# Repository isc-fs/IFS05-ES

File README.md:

# IFS05 - ELECTRONIC SUBSYSTEMS

Repositorio para el departamento de Electronic Subsystems del IFS05 de la temporada 2022/2023.

## Primeros pasos:
1. Crea una cuenta en GitHub si aún no tienes una.
2. Descarga e instala [GitHub Desktop](https://desktop.github.com/) (básico) o [Git CLI](https://git-scm.com/book/en/v2/Getting-Started-Installing-Git) (avanzado).

    * Si es la primera vez que utilizas GitHub Desktop, asegúrate de leer el [Manual del usuario](https://help.github.com/desktop/guides/).
    * Si estás usando Git por primera vez, deberías empezar leyendo un tutorial. Hay muchos disponibles en línea:
        * [Tutorial de Git](https://git-scm.com/docs/gittutorial)
        * [Atlassian Git Tutorial](https://www.atlassian.com/git/tutorials/)
    * Puede que quieras guardar una copia de [GitHub's Git Cheat Sheet](https://services.github.com/kit/downloads/github-git-cheat-sheet.pdf) como referencia.

3. Habla con tu jefe de departamento para que te añada al equipo dentro de la organización de GitHub.
4. Clona este repositorio en tu ordenador utilizando las URLs:
    * SSH: `git@github.com:isc-fs/IFS05-ES.git`
    * HTTPS: `https://github.com/isc-fs/IFS05-ES.git`

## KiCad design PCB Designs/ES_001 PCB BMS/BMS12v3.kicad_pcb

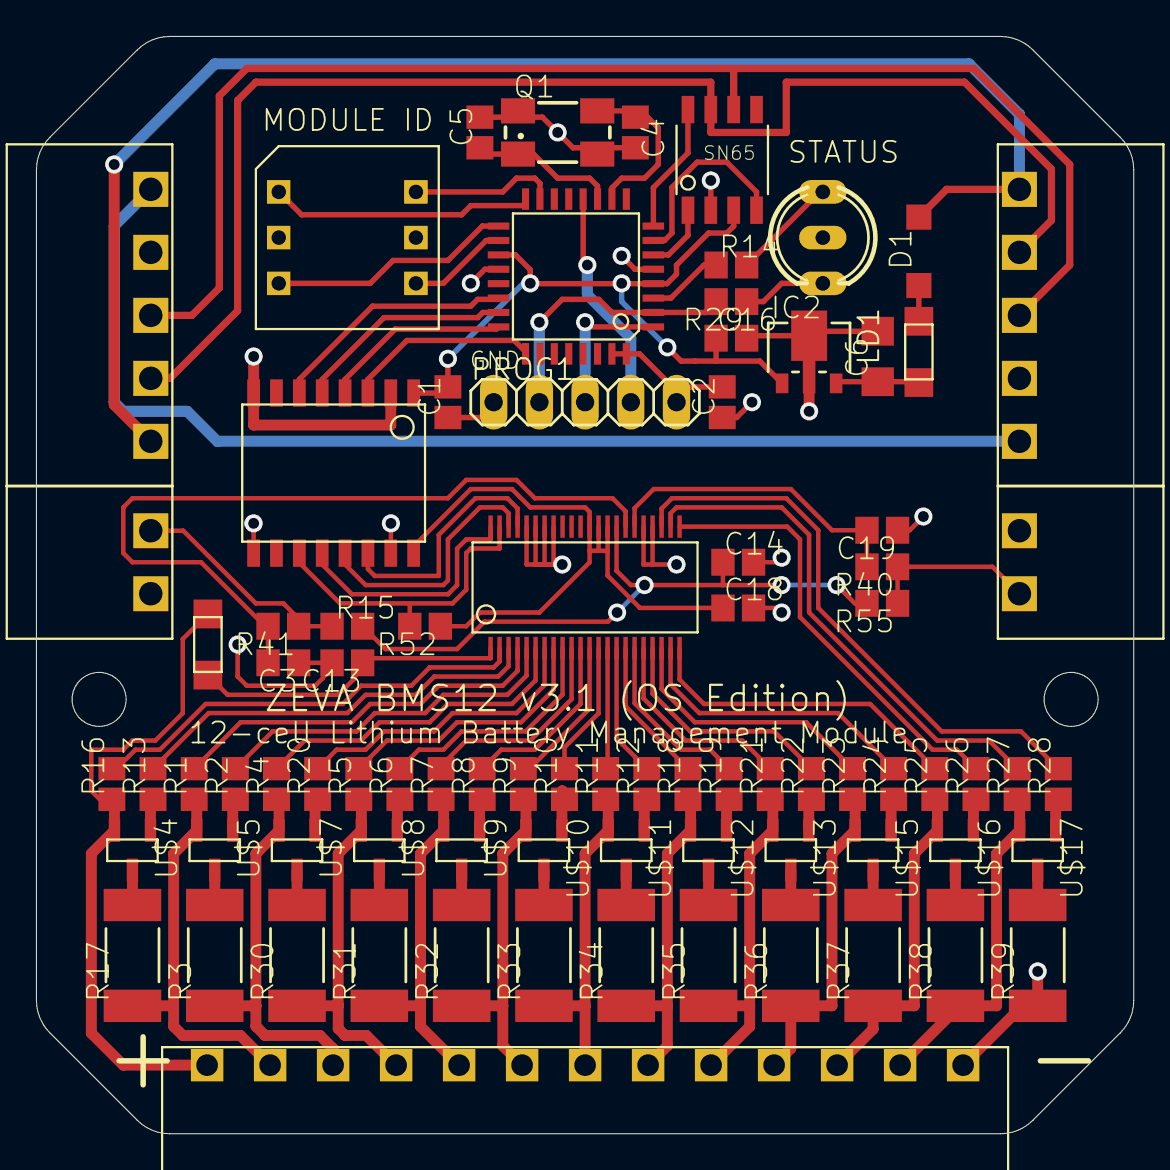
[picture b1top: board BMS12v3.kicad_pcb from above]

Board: 2 copper layers, 61.0 x 61.0 mm, 85 parts (0 on the bottom side), 100 nets.

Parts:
@HOLE0, @HOLE1: (no value)
C1, C2, C3, C13, C14, C18, C19: 0.1uF; C0805
C4, C5: 10pF; C0805
C6: 47uF; C1206
C16: 1uF; C0805
D1: DIODE-SOD123; SOD123
IC2: 78LXXSOT89; SOT89R
LD1: DUOLED-RG-C; DUOLED-C-5MM
PROG1: PINHD-1X5; 1X05
Q1: CRYSTALCTS406; CTS406
R1, R2, R4, R5, R6, R7, R8, R9, R10, R11, R12, R13, R14, R16, R18, R19, R20, R21, R22, R23, R24, R25, R26, R27, R28, R29: 3.3K; R0805
R3, R17, R30, R31, R32, R33, R34, R35, R36, R37, R38, R39: 50R; R2512
R15, R40, R41, R52, R55: 100K; R0805
SN65: L9616; SOIC8
U$1: LTC6802-2; SSOP-44
U$2, U$19: MOLEX-39502-1005
U$3: ATMEGA16M1; TQFP32
U$4, U$5, U$7, U$8, U$9, U$10, U$11, U$12, U$13, U$15, U$16, U$17: SI2351DS; SOT23
U$6, U$28: 50mA PTC; 1206
U$14: ADUM1411; SOIC16W
U$18: MOLEX_TERM_BLOCK_13
U$20, U$21: MOLEX-39502-1002
U$31: SH-7000WURTH; WS-ROTV

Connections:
+5V: C1.2, C16.1, IC2.2 (OUT), SN65.P$3 (VS), U$3.4 (VCC), U$3.19 (AVCC), U$14.1 (VDD1)
+12V: D1.A, U$2.1, U$19.1
/VIA: U$3.25 (PC7(D2A/AMP2+)), U$14.3 (VIA)
/VIB: U$3.24 (PB4(AMP0+)), U$14.4 (VIB)
/VIC: U$3.23 (PB3(AMP0-)), U$14.5 (VIC)
/VOD: U$3.22 (PC6(ADC10/ACMP1)), U$14.6 (VOD)
AGND: C3.1, C13.2, C14.2, C18.2, C19.1, R39.1, U$1.26 (V-), U$1.27 (NC), U$1.37 (A0), U$1.38 (A1), U$1.39 (A2), U$1.40 (A3), U$14.9 (GND2B), U$14.15 (GND2), U$18.13, U$20.1, U$21.1
GND: C1.1, C2.1, C4.2, C5.2, C6.2, C16.2, IC2.4 (GND), LD1.C, PROG1.1, SN65.P$2 (GND), U$2.4, U$3.5 (GND), U$3.20 (AGND), U$14.2 (GND1), U$14.8 (GND1B), U$19.4, U$31.C, U$31.C2 (C_)
unnamed: C2.2, PROG1.5, U$3.31 (PE0(/RESET)), U$3.32 (PD1(PSCIN0/CLK0))
unnamed: C3.2, R41.2, U$1.29 (VTEMP2)
unnamed: C4.1, Q1.3 (2), U$3.10 (PE1(XTAL1/OC0B))
unnamed: C5.1, Q1.1, U$3.11 (PE2(XTAL2/ADC0))
unnamed: C6.1, IC2.1 (IN), U$28.P$2
unnamed: C13.1, U$1.1 (V+), U$6.P$2
unnamed: C14.1, R15.2, R55.2, U$1.30 (VREF)
unnamed: C18.1, R52.1, U$1.31 (VREG), U$1.32 (TOS), U$1.33 (MMB), U$14.16 (VDD2)
unnamed: C19.2, R40.2, U$1.28 (VTEMP1)
unnamed: D1.C, U$28.P$1
unnamed: LD1.AR, R29.1
unnamed: LD1.AX (AG), R14.2
unnamed: PROG1.2, R29.2, U$3.2 (PD3(TXLIN/OC0A/SS/MOSI_A))
unnamed: PROG1.3, U$3.1 (PD2(PSCIN2/OC1A/MISO_A))
unnamed: PROG1.4, U$3.12 (PD4(ADC1/RXD/RXLIN/ICP1A/SCK_A))
unnamed: R1.1, R17.1, U$5.P$2 (S), U$18.2
unnamed: R1.2, U$1.4 (C11)
unnamed: R2.1, U$5.P$1 (G)
unnamed: R2.2, U$1.5 (S11)
unnamed: R3.1, R4.1, U$7.P$2 (S), U$18.3
unnamed: R3.2, U$5.P$3 (D)
unnamed: R4.2, U$1.6 (C10)
unnamed: R5.2, U$1.8 (C9)
unnamed: R6.1, U$8.P$1 (G)
unnamed: R6.2, U$1.9 (S9)
unnamed: R7.2, U$1.10 (C8)
unnamed: R8.1, U$9.P$1 (G)
unnamed: R8.2, U$1.11 (S8)
unnamed: R9.2, U$1.12 (C7)
unnamed: R10.1, U$10.P$1 (G)
unnamed: R10.2, U$1.13 (S7)
unnamed: R11.1, R33.1, U$11.P$2 (S), U$18.7
unnamed: R11.2, U$1.14 (C6)
unnamed: R12.1, U$11.P$1 (G)
unnamed: R12.2, U$1.15 (S6)
unnamed: R13.1, U$4.P$1 (G)
unnamed: R13.2, U$1.3 (S12)
unnamed: R14.1, U$3.3 (PC1(PSCIN1/OC1B/SS_A))
unnamed: R15.1, R41.1, U$21.2
unnamed: R16.1, U$4.P$2 (S), U$6.P$1, U$18.1
unnamed: R16.2, U$1.2 (C12)
unnamed: R17.2, U$4.P$3 (D)
unnamed: R18.1, R34.1, U$12.P$2 (S), U$18.8
unnamed: R18.2, U$1.16 (C5)
unnamed: R19.1, U$12.P$1 (G)
unnamed: R19.2, U$1.17 (S5)
unnamed: R20.1, U$7.P$1 (G)
unnamed: R20.2, U$1.7 (S10)
unnamed: R21.1, R35.1, U$13.P$2 (S), U$18.9
unnamed: R21.2, U$1.18 (C4)
unnamed: R22.1, U$13.P$1 (G)
unnamed: R22.2, U$1.19 (S4)
unnamed: R23.1, R36.1, U$15.P$2 (S), U$18.10
unnamed: R23.2, U$1.20 (C3)
unnamed: R24.1, U$15.P$1 (G)
unnamed: R24.2, U$1.21 (S3)
unnamed: R25.1, R37.1, U$16.P$2 (S), U$18.11
unnamed: R25.2, U$1.22 (C2)
unnamed: R26.1, U$16.P$1 (G)
unnamed: R26.2, U$1.23 (S2)
unnamed: R27.1, R38.1, U$17.P$2 (S), U$18.12
unnamed: R27.2, U$1.24 (C1)
unnamed: R28.1, U$17.P$1 (G)
unnamed: R28.2, U$1.25 (S1)
unnamed: R5.1, R30.1, U$8.P$2 (S), U$18.4
unnamed: R30.2, U$7.P$3 (D)
unnamed: R7.1, R31.1, U$9.P$2 (S), U$18.5
unnamed: R31.2, U$8.P$3 (D)
unnamed: R9.1, R32.1, U$10.P$2 (S), U$18.6
unnamed: R32.2, U$9.P$3 (D)
unnamed: R33.2, U$10.P$3 (D)
unnamed: R34.2, U$11.P$3 (D)
unnamed: R35.2, U$12.P$3 (D)
unnamed: R36.2, U$13.P$3 (D)
unnamed: R37.2, U$15.P$3 (D)
unnamed: R38.2, U$16.P$3 (D)
unnamed: R39.2, U$17.P$3 (D)
unnamed: R40.1, R55.1, U$20.2
unnamed: R52.2, U$1.43 (SDO), U$14.11 (VID)
unnamed: SN65.P$1 (TX0), U$3.6 (PC2(T0/TXCAN))
unnamed: SN65.P$4 (RX0), U$3.7 (PC3(T1/RXCAN/ICP1B))
unnamed: SN65.P$6 (C_L), U$2.3, U$19.3
unnamed: SN65.P$7 (C_H), U$2.2, U$19.2
unnamed: SN65.P$8 (ASC), U$3.8 (PB0(MISO/PSCOUT2A))
unnamed: U$1.41 (SCKI), U$14.14 (VOA)
unnamed: U$1.42 (SDI), U$14.13 (VOB)
unnamed: U$1.44 (CSBI), U$14.12 (VOC)
unnamed: U$3.15 (PD7(ACMP0)), U$31.8
unnamed: U$3.16 (PB2(ADC5/INT1/ACMPN0)), U$31.1
unnamed: U$3.17 (PC4(ADC8/ACMPN3/AMP1-)), U$31.4
unnamed: U$3.18 (PC5(ADC9/ACMP3/AMP1+)), U$31.2
unnamed: U$2.5, U$19.5

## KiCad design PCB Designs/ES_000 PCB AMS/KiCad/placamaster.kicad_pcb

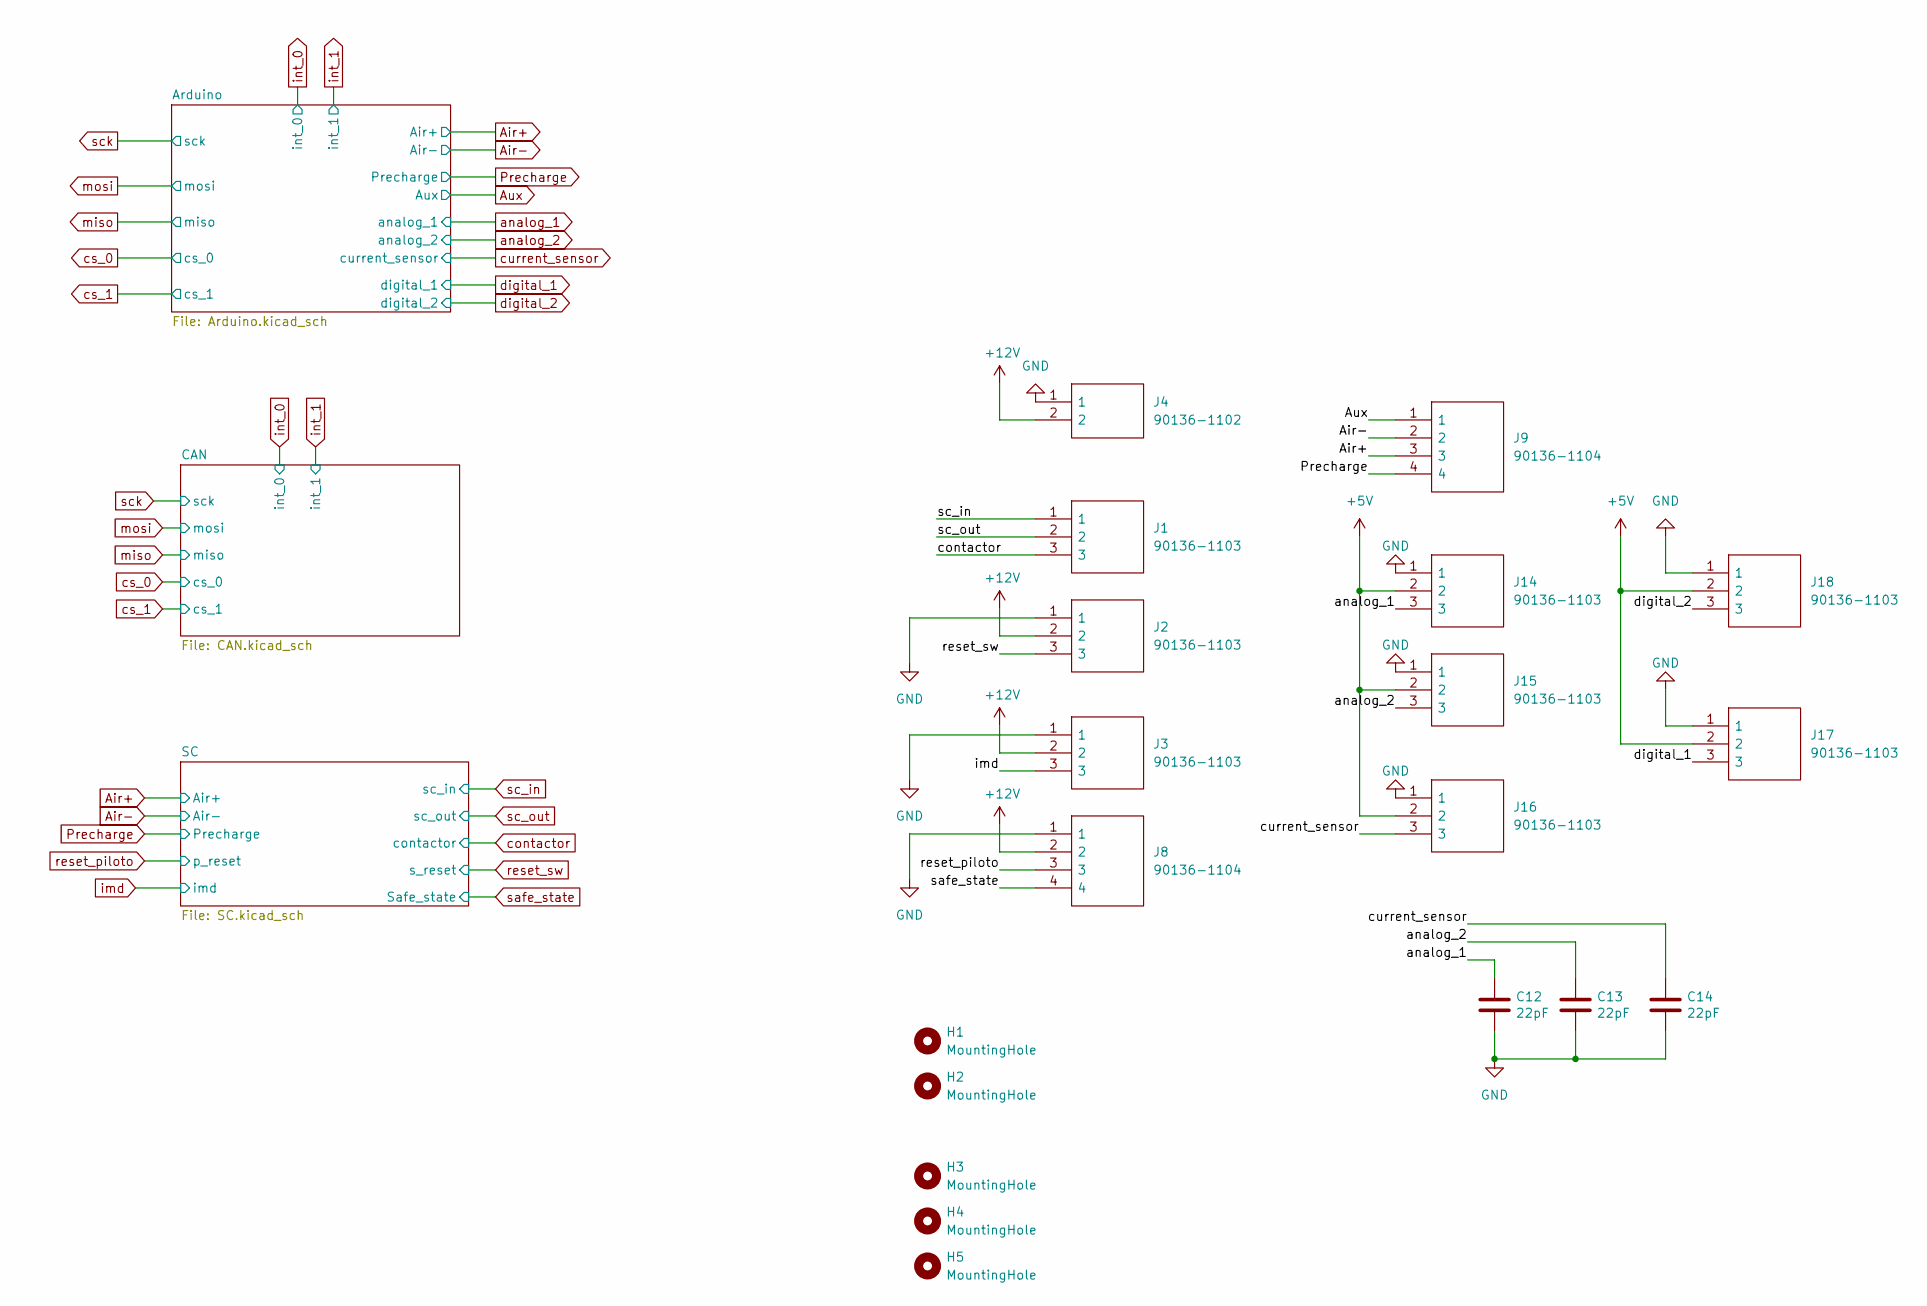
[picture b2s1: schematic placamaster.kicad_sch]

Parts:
C12, C13, C14: 22pF; C_0805_2012Metric_Pad1.18x1.45mm_HandSolder
H1, H2, H3, H4, H5: MountingHole
J1, J2, J3, J14, J15, J16, J17, J18: 90136-1103; SHDR3W65P0X254_1X3_1097X721X1110P; Mouser Part Number 538-90136-1103
J4: 90136-1102; SHDR2W65P0X254_1X2_843X721X1110P; Mouser Part Number 538-90136-1102
J8, J9: 90136-1104; SHDR4W65P0X254_1X4_1351X721X1110P; Mouser Part Number 538-90136-1104

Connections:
+5V: J14.2, J15.2, J16.2, J17.2, J18.2; also elsewhere on the board
+12V: J2.2, J3.2, J4.2, J8.2; also elsewhere on the board
Air+: J9.3; also elsewhere on the board
Air-: J9.2; also elsewhere on the board
Aux: J9.1; also elsewhere on the board
GND: C12.2, C13.2, C14.2, J2.1, J3.1, J4.1, J8.1, J14.1, J15.1, J16.1, J17.1, J18.1; also elsewhere on the board
Precharge: J9.4; also elsewhere on the board
analog_1: C12.1, J14.3; also elsewhere on the board
analog_2: C13.1, J15.3; also elsewhere on the board
contactor: J1.3; also elsewhere on the board
current_sensor: C14.1, J16.3; also elsewhere on the board
digital_1: J17.3; also elsewhere on the board
digital_2: J18.3; also elsewhere on the board
imd: J3.3; also elsewhere on the board
reset_piloto: J8.3; also elsewhere on the board
reset_sw: J2.3; also elsewhere on the board
safe_state: J8.4; also elsewhere on the board
sc_in: J1.1; also elsewhere on the board
sc_out: J1.2; also elsewhere on the board

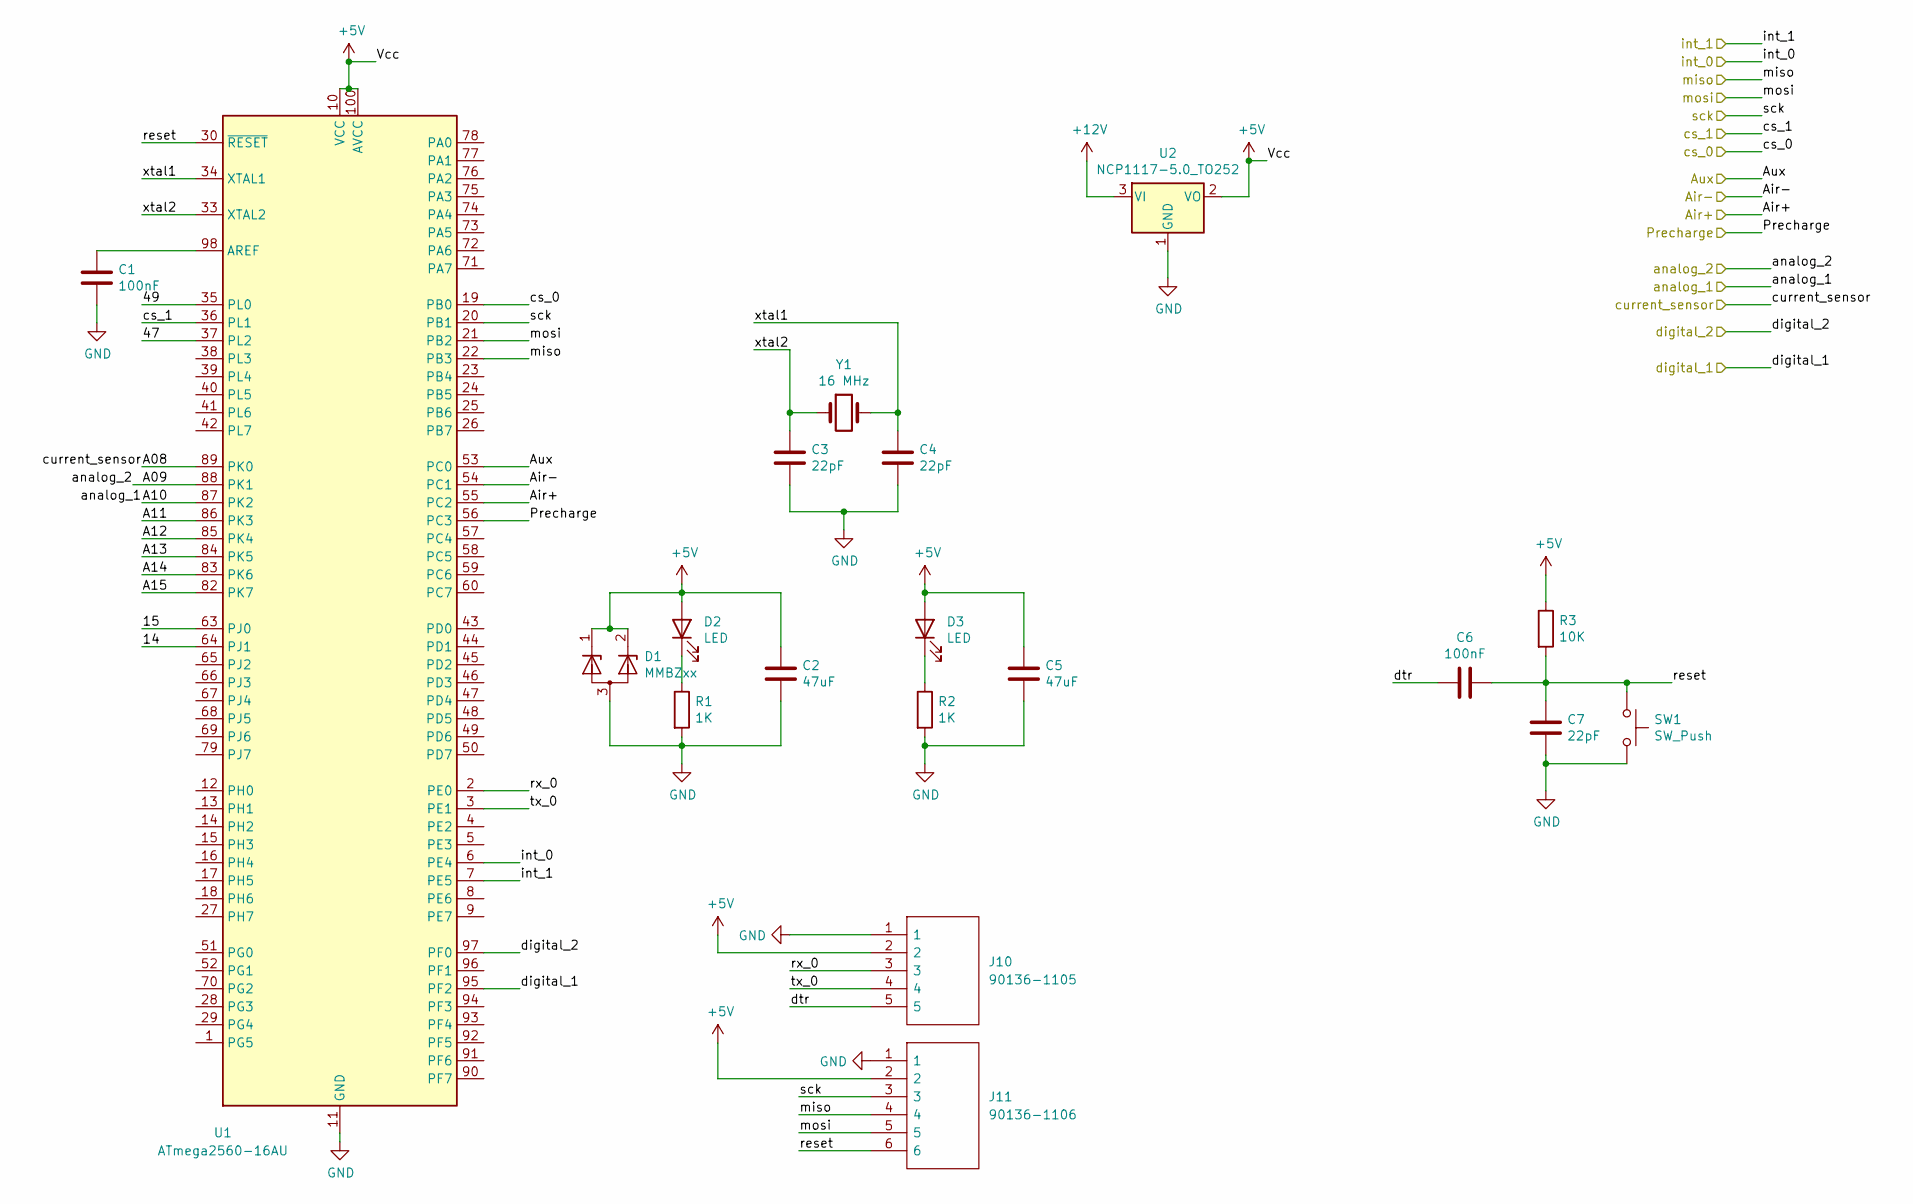
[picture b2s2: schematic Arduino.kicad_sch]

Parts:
C1, C6: 100nF; C_0805_2012Metric_Pad1.18x1.45mm_HandSolder
C2, C5: 47uF; C_0805_2012Metric_Pad1.18x1.45mm_HandSolder
C3, C4, C7: 22pF; C_0805_2012Metric_Pad1.18x1.45mm_HandSolder
D1: MMBZxx; SOT-23
D2, D3: LED; Led5V
J10: 90136-1105; SHDR5W65P0X254_1X5_1605X721X1110P; Mouser Part Number 538-90136-1105
J11: 90136-1106; SHDR6W65P0X254_1X6_1859X721X1110P; Mouser Part Number 538-90136-1106
R1, R2: 1K; R_0805_2012Metric_Pad1.20x1.40mm_HandSolder
R3: 10K; R_0805_2012Metric_Pad1.20x1.40mm_HandSolder
SW1: SW_Push; 1301931424
U1: ATmega2560-16AU; TQFP-100_14x14mm_P0.5mm
U2: NCP1117-5.0_TO252; TO-252-2
Y1: 16 MHz; ECS-80-32-1X

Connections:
+5V: C2.1, C5.1, D1.1 (K), D1.2 (K), D2.2 (A), D3.2 (A), J10.2, J11.2, R3.1, U1.10 (VCC), U1.31 (VCC), U1.61 (VCC), U1.80 (VCC), U1.100 (AVCC), U2.2 (VO); also elsewhere on the board
+12V: U2.3 (VI); also elsewhere on the board
/Arduino/14: U1.64 (PJ1)
/Arduino/15: U1.63 (PJ0)
/Arduino/47: U1.37 (PL2)
/Arduino/49: U1.35 (PL0)
/Arduino/A11: U1.86 (PK3)
/Arduino/A12: U1.85 (PK4)
/Arduino/A13: U1.84 (PK5)
/Arduino/A14: U1.83 (PK6)
/Arduino/A15: U1.82 (PK7)
/Arduino/dtr: C6.2, J10.5
/Arduino/reset: C6.1, C7.2, J11.6, R3.2, SW1.1, U1.30 (~RESET)
/Arduino/rx_0: J10.3, U1.2 (PE0)
/Arduino/tx_0: J10.4, U1.3 (PE1)
/Arduino/xtal1: C4.1, U1.34 (XTAL1), Y1.2
/Arduino/xtal2: C3.1, U1.33 (XTAL2), Y1.1
Air+: U1.55 (PC2); also elsewhere on the board
Air-: U1.54 (PC1); also elsewhere on the board
Aux: U1.53 (PC0); also elsewhere on the board
GND: C1.2, C2.2, C3.2, C4.2, C5.2, C7.1, D1.3 (A), J10.1, J11.1, R1.2, R2.2, SW1.2, U1.11 (GND), U1.32 (GND), U1.62 (GND), U1.81 (GND), U1.99 (GND), U2.1 (GND); also elsewhere on the board
unnamed: C1.1, U1.98 (AREF)
unnamed: D2.1 (K), R1.1
unnamed: D3.1 (K), R2.1
Precharge: U1.56 (PC3); also elsewhere on the board
analog_1: U1.87 (PK2); also elsewhere on the board
analog_2: U1.88 (PK1); also elsewhere on the board
cs_0: U1.19 (PB0); also elsewhere on the board
cs_1: U1.36 (PL1); also elsewhere on the board
current_sensor: U1.89 (PK0); also elsewhere on the board
digital_1: U1.95 (PF2); also elsewhere on the board
digital_2: U1.97 (PF0); also elsewhere on the board
int_0: U1.6 (PE4); also elsewhere on the board
int_1: U1.7 (PE5); also elsewhere on the board
miso: J11.4, U1.22 (PB3); also elsewhere on the board
mosi: J11.5, U1.21 (PB2); also elsewhere on the board
sck: J11.3, U1.20 (PB1); also elsewhere on the board

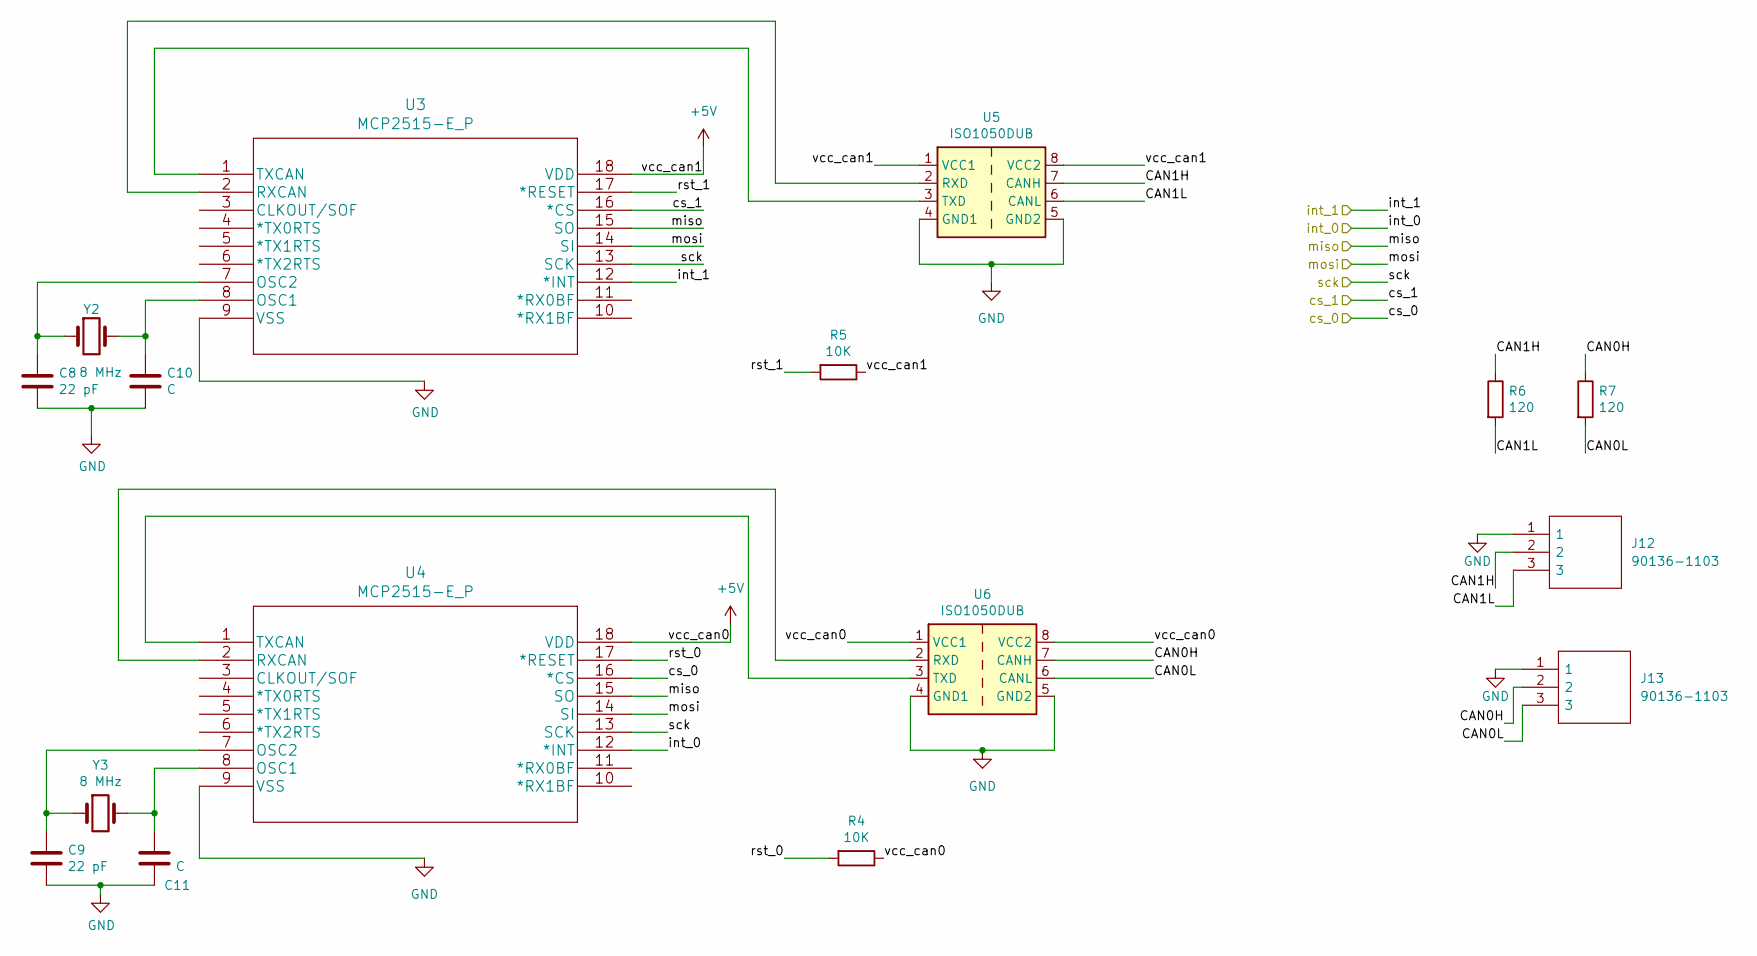
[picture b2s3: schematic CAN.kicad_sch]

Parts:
C8, C9: 22 pF; C_0805_2012Metric_Pad1.18x1.45mm_HandSolder
C10, C11: C; C_0805_2012Metric_Pad1.18x1.45mm_HandSolder
J12, J13: 90136-1103; SHDR3W65P0X254_1X3_1097X721X1110P; Mouser Part Number 538-90136-1103
R4, R5: 10K; R_0805_2012Metric_Pad1.20x1.40mm_HandSolder
R6, R7: 120; R_0805_2012Metric_Pad1.20x1.40mm_HandSolder
U3, U4: MCP2515-E_P; SOIC127P1030X265-18N
U5, U6: ISO1050DUB; SOP-8_6.62x9.15mm_P2.54mm
Y2, Y3: 8 MHz; ECS-80-32-1X

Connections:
+5V: R4.1, R5.1, U3.18 (VDD), U4.18 (VDD), U5.1 (VCC1), U5.8 (VCC2), U6.1 (VCC1), U6.8 (VCC2); also elsewhere on the board
/CAN/CAN0H: J13.2, R7.1, U6.7 (CANH)
/CAN/CAN0L: J13.3, R7.2, U6.6 (CANL)
/CAN/CAN1H: J12.2, R6.1, U5.7 (CANH)
/CAN/CAN1L: J12.3, R6.2, U5.6 (CANL)
/CAN/rst_0: R4.2, U4.17 (*RESET)
/CAN/rst_1: R5.2, U3.17 (*RESET)
GND: C8.2, C9.2, C10.2, C11.2, J12.1, J13.1, U3.9 (VSS), U4.9 (VSS), U5.4 (GND1), U5.5 (GND2), U6.4 (GND1), U6.5 (GND2); also elsewhere on the board
unnamed: C8.1, U3.7 (OSC2), Y2.1
unnamed: C9.1, U4.7 (OSC2), Y3.1
unnamed: C10.1, U3.8 (OSC1), Y2.2
unnamed: C11.1, U4.8 (OSC1), Y3.2
unnamed: U3.1 (TXCAN), U5.3 (TXD)
unnamed: U3.2 (RXCAN), U5.2 (RXD)
unnamed: U4.1 (TXCAN), U6.3 (TXD)
unnamed: U4.2 (RXCAN), U6.2 (RXD)
cs_0: U4.16 (*CS); also elsewhere on the board
cs_1: U3.16 (*CS); also elsewhere on the board
int_0: U4.12 (*INT); also elsewhere on the board
int_1: U3.12 (*INT); also elsewhere on the board
miso: U3.15 (SO), U4.15 (SO); also elsewhere on the board
mosi: U3.14 (SI), U4.14 (SI); also elsewhere on the board
sck: U3.13 (SCK), U4.13 (SCK); also elsewhere on the board

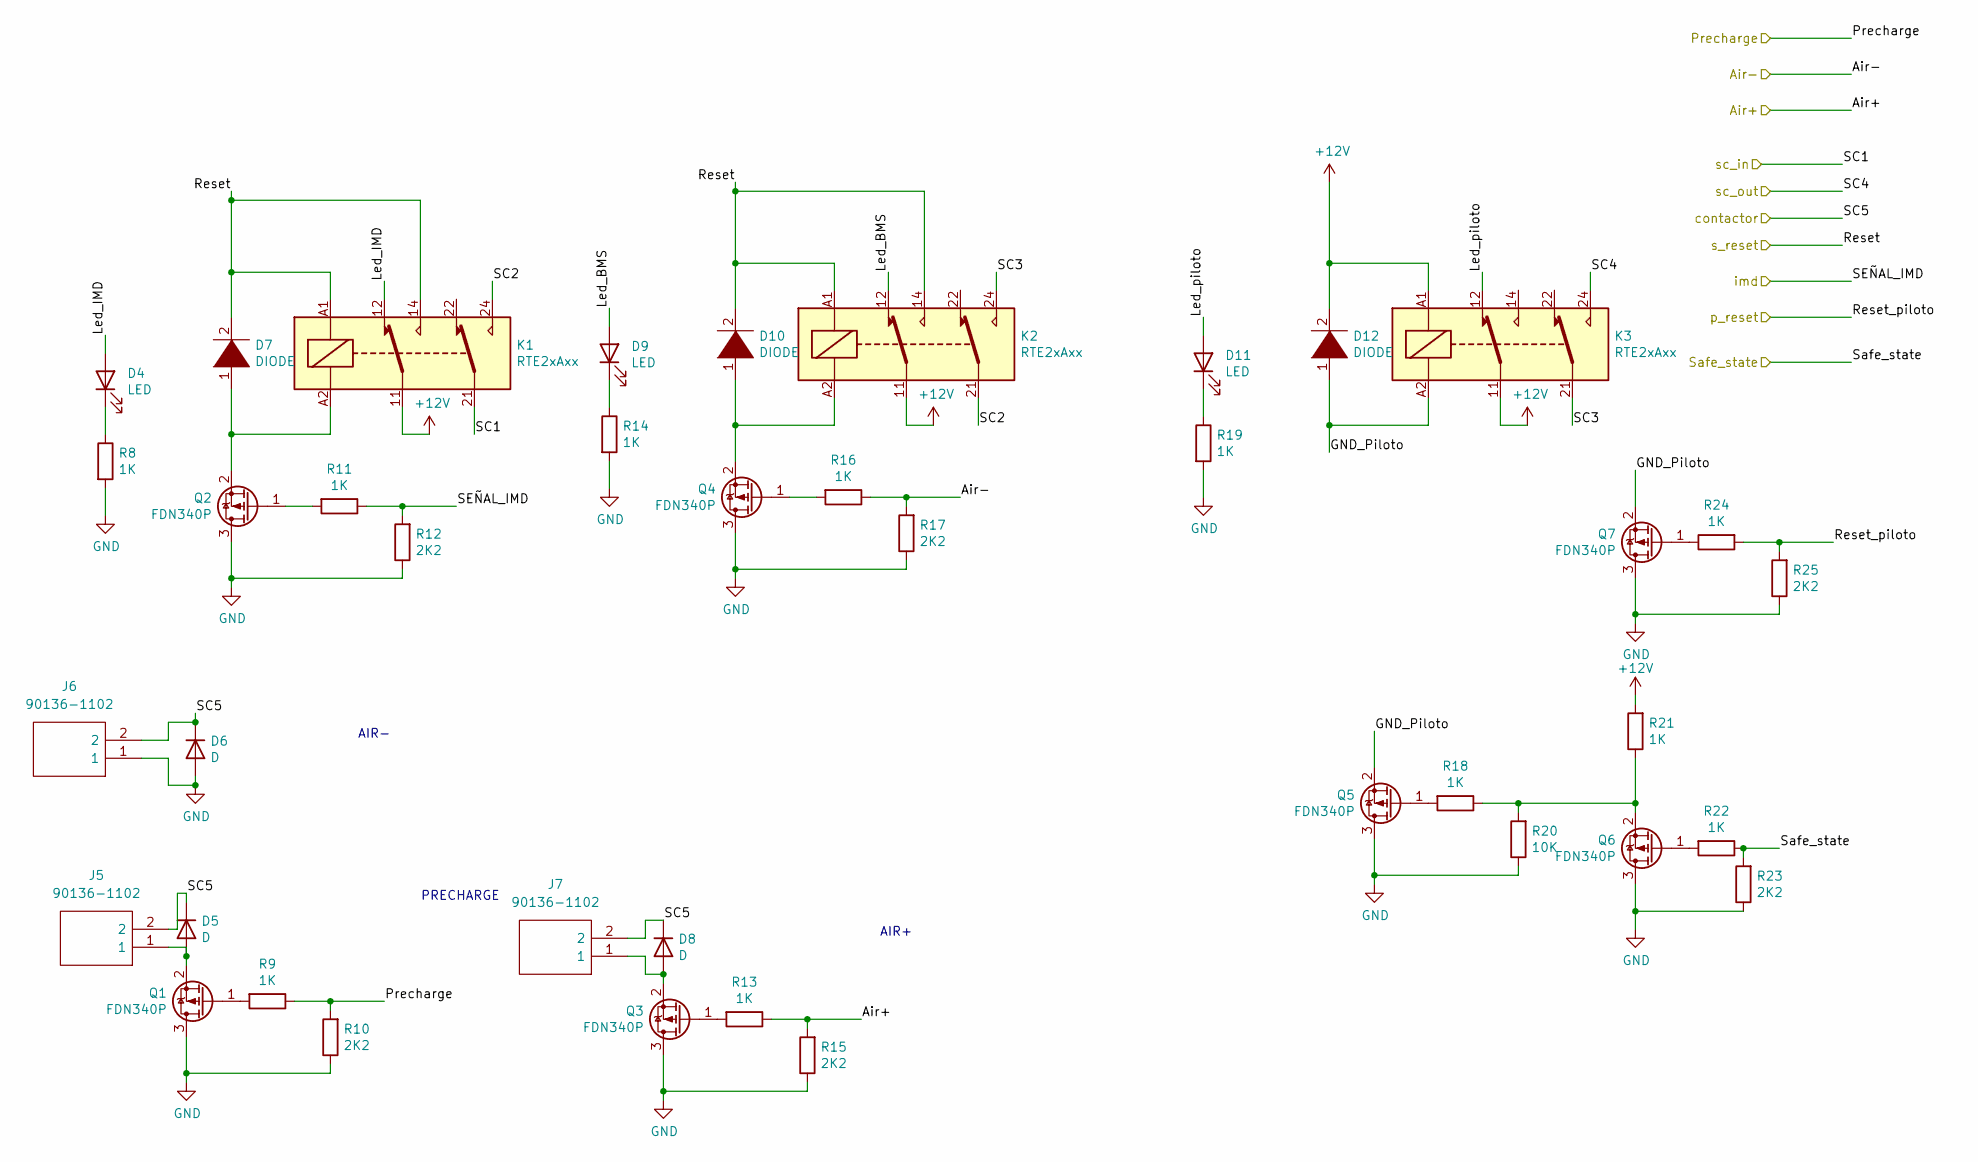
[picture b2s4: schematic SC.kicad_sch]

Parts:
D4, D9, D11: LED; Led5V
D5, D6, D8: D; D_0805_2012Metric_Pad1.15x1.40mm_HandSolder
D7, D10, D12: DIODE; D_0805_2012Metric_Pad1.15x1.40mm_HandSolder
J5, J6, J7: 90136-1102; SHDR2W65P0X254_1X2_843X721X1110P; Mouser Part Number 538-90136-1102
K1, K2, K3: RTE2xAxx; Relay_DPDT_Schrack-RT2-FormC_RM5mm
Q1, Q2, Q3, Q4, Q5, Q6, Q7: FDN340P; SOT-23
R8, R9, R11, R13, R14, R16, R18, R19, R21, R22, R24: 1K; R_0805_2012Metric_Pad1.20x1.40mm_HandSolder
R10, R12, R15, R17, R23, R25: 2K2; R_0805_2012Metric_Pad1.20x1.40mm_HandSolder
R20: 10K; R_0805_2012Metric_Pad1.20x1.40mm_HandSolder

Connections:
+12V: D12.2 (A), K1.11, K2.11, K3.11, K3.A1, R21.2; also elsewhere on the board
/SC/GND_Piloto: D12.1 (K), K3.A2, Q5.2 (S), Q7.2 (S)
/SC/Led_BMS: D9.2 (A), K2.12
/SC/Led_IMD: D4.2 (A), K1.12
/SC/Led_piloto: D11.2 (A), K3.12
/SC/SC2: K1.24, K2.21
/SC/SC3: K2.24, K3.21
Air+: R13.1, R15.2; also elsewhere on the board
Air-: R16.1, R17.2; also elsewhere on the board
GND: D6.2 (A), J6.1, Q1.3 (D), Q2.3 (D), Q3.3 (D), Q4.3 (D), Q5.3 (D), Q6.3 (D), Q7.3 (D), R8.2, R10.1, R12.1, R14.2, R15.1, R17.1, R19.2, R20.1, R23.1, R25.1; also elsewhere on the board
unnamed: D4.1 (K), R8.1
unnamed: D7.1 (K), K1.A2, Q2.2 (S)
unnamed: D8.2 (A), J7.1, Q3.2 (S)
unnamed: D9.1 (K), R14.1
unnamed: D10.1 (K), K2.A2, Q4.2 (S)
unnamed: D11.1 (K), R19.1
unnamed: D5.2 (A), J5.1, Q1.2 (S)
unnamed: Q1.1 (G), R9.2
unnamed: Q2.1 (G), R11.2
unnamed: Q3.1 (G), R13.2
unnamed: Q4.1 (G), R16.2
unnamed: Q5.1 (G), R18.2
unnamed: Q6.1 (G), R22.2
unnamed: Q6.2 (S), R18.1, R20.2, R21.1
unnamed: Q7.1 (G), R24.1
Precharge: R9.1, R10.2; also elsewhere on the board
contactor: D5.1 (K), D6.1 (K), D8.1 (K), J5.2, J6.2, J7.2; also elsewhere on the board
imd: R11.1, R12.2; also elsewhere on the board
reset_piloto: R24.2, R25.2; also elsewhere on the board
reset_sw: D7.2 (A), D10.2 (A), K1.14, K1.A1, K2.14, K2.A1; also elsewhere on the board
safe_state: R22.1, R23.2; also elsewhere on the board
sc_in: K1.21; also elsewhere on the board
sc_out: K3.24; also elsewhere on the board

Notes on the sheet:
AIR+
PRECHARGE
AIR-

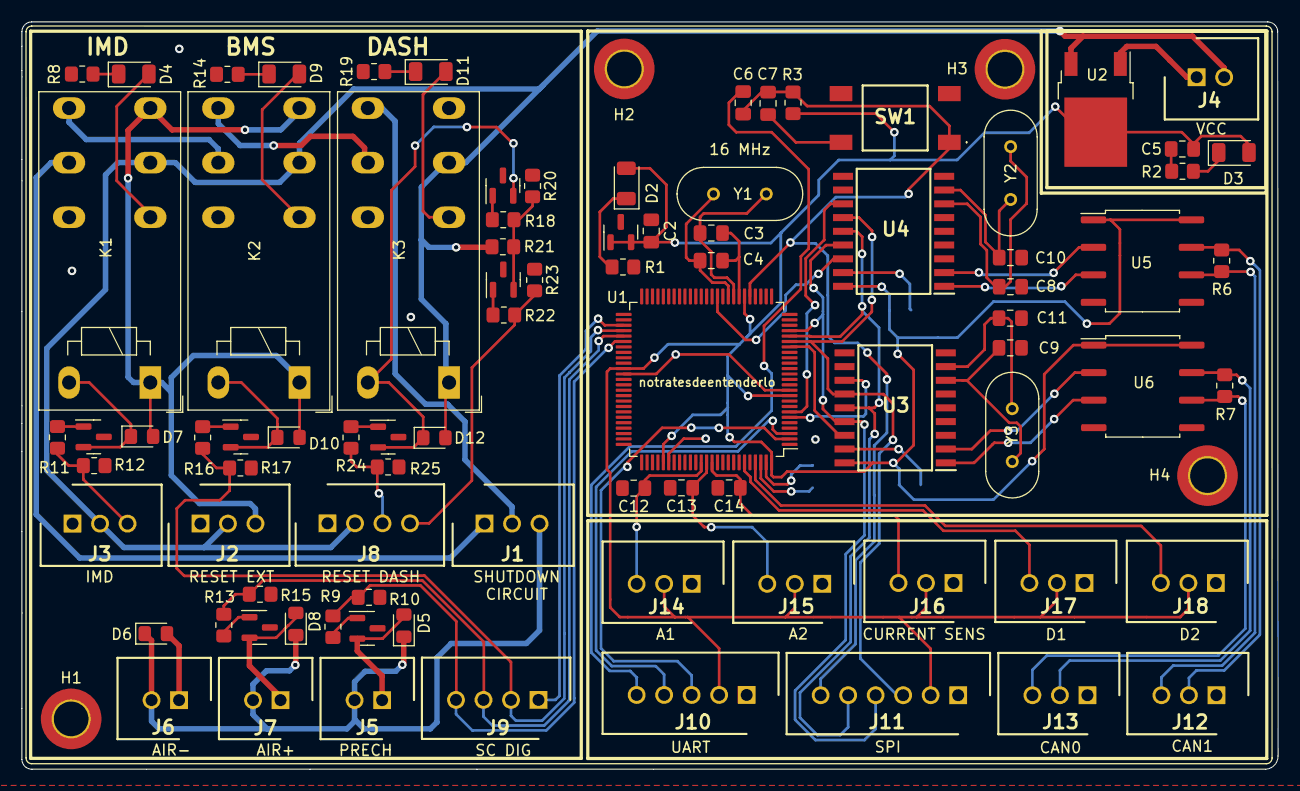
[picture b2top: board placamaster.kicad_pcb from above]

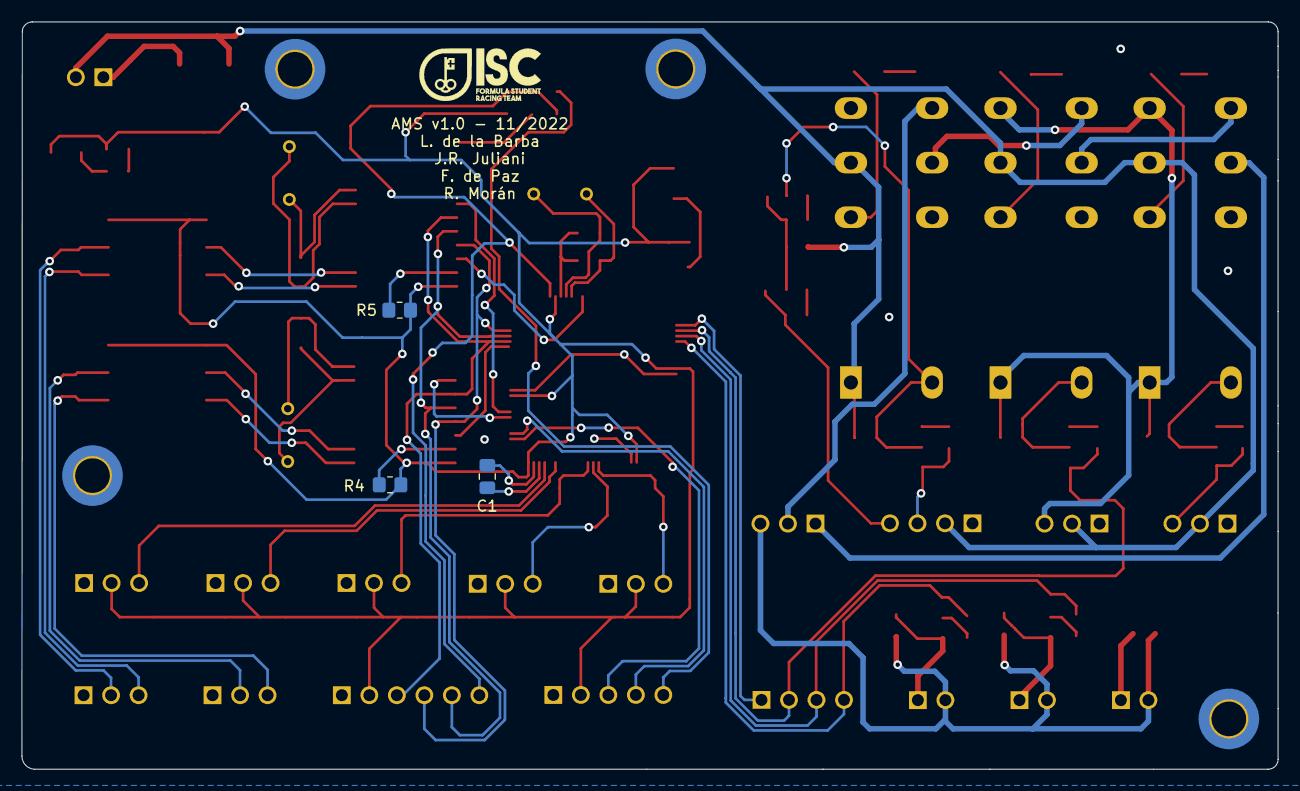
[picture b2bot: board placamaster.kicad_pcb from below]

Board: 2 copper layers, 116.0 x 69.0 mm, 93 parts (3 on the bottom side), 70 nets.

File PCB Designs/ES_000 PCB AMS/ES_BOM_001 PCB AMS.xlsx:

Reference(s) | Qty | Value | Footprint | Price | Total price | Manufacturer_Name | Mouser Part Number | Mouser Price/Stock
C1, C6 | 2 | 100nF | Capacitor_SMD:C_0805_2012Metric_Pad1.18x1.45mm_HandSolder | 0.1 | 0.2 | KEMET | 80-C0805C104K8RAUTO | https://www.mouser.es/ProductDetail/KEMET/C0805C104K8RACAUTO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
C2, C5 | 2 | 47uF | Capacitor_SMD:C_0805_2012Metric_Pad1.18x1.45mm_HandSolder | 0.56999999999999995 | 1.1399999999999999 | Murata Electronics | 81-GRM21BR61A476ME5L | https://www.mouser.es/ProductDetail/Murata-Electronics/GRM21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
C3, C4, C7, C8, C9, C10, C11, C12, C13, C14 | 10 | 22pF | Capacitor_SMD:C_0805_2012Metric_Pad1.18x1.45mm_HandSolder | 0.3 | 3 | KEMET | 80-C0805C220J8GAUTO | https://www.mouser.es/ProductDetail/KEMET/C0805C220J8GACAUTO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
D1 | 1 | MMBZxx | Package_TO_SOT_SMD:SOT-23 | 0.36 | 0.36 | Diodes Incorporated | 621-MMBZ5232BW-F | https://www.mouser.es/ProductDetail/Diodes-Incorporated/MMBZ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
D2, D3, D4, D9, D11 | 5 | LED | Led5V:Led5V | 0.42 | 2.1 | Stanley Electric | 327-PG1101WTR | https://www.mouser.es/ProductDetail/Stanley-Electric/PG1101W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
D5, D6, D8, D7, D10, D12 | 6 | D | Diode_SMD:D_0805_2012Metric_Pad1.15x1.40mm_HandSolder | 0.32 | 1.92 | Wurth Elektronik | 710-82350120101 | https://www.mouser.es/ProductDetail/Wurth-Elektronik/8235012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
H1, H2, H3, H4, H5 | 5 | MountingHole |  |  | 0
J1, J2, J3, J14, J15, J16, J17, J18, J12, J13 | 10 | 90136-1103 | Conector 3 pin C-grid:SHDR3W65P0X254_1X3_1097X721X1110P | 1.57 | 15.700000000000001 | Molex | 538-90136-1103 | https://www.mouser.co.uk/ProductDetail/Molex/90136-1103?qs=k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
J4, J5, J6, J7 | 4 | 90136-1102 | Conector 2 pin C-grid:SHDR2W65P0X254_1X2_843X721X1110P | 1.17 | 4.68 | Molex | 538-90136-1102 | https://www.mouser.co.uk/ProductDetail/Molex/90136-1102?qs=k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
J8, J9 | 2 | 90136-1104 | Conector 4 pin C-grd:SHDR4W65P0X254_1X4_1351X721X1110P | 1.33 | 2.66 | Molex | 538-90136-1104 | https://www.mouser.co.uk/ProductDetail/Molex/90136-1104?qs=T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
J10 | 1 | 90136-1105 | Conector 5 pin C-grid:SHDR5W65P0X254_1X5_1605X721X1110P | 1.57 | 1.57 | Molex | 538-90136-1105 | https://www.mouser.co.uk/ProductDetail/Molex/90136-1105?qs=T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
J11 | 1 | 90136-1106 | Conector 6 pin C-grid:SHDR6W65P0X254_1X6_1859X721X1110P | 1.45 | 1.45 | Molex | 538-90136-1106 | https://www.mouser.co.uk/ProductDetail/Molex/90136-1106?qs=k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
K1, K2, K3 | 3 | RTE2xAxx | Relay_THT:Relay_DPDT_Schrack-RT2-FormC_RM5mm |  | 0
Q1, Q2, Q3, Q4, Q5, Q6, Q7 | 7 | FDN5632N | Package_TO_SOT_SMD:SOT-23 | 0.7 | 4.8999999999999995 | Fairchild | 512-FDN5632N-F085 | https://www.mouser.es/ProductDetail/onsemi-Fairchild/FDN5632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
R1, R2, R8, R9, R11, R13, R14, R16, R18, R19, R21, R22, R24 | 13 | 1K | Resistor_SMD:R_0805_2012Metric_Pad1.20x1.40mm_HandSolder | 0.1 | 1.3 | TE Connectivity | 279-1623131-1 | https://www.mouser.es/ProductDetail/TE-Connectivity-Holswort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
R3, R4, R5, R20 | 4 | 10K | Resistor_SMD:R_0805_2012Metric_Pad1.20x1.40mm_HandSolder | 0.21 | 0.84 | TE Connectivity | 279-1623097-1 | https://www.mouser.es/ProductDetail/TE-Connectivity-Holswort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
R6, R7 | 2 | 120 | Resistor_SMD:R_0805_2012Metric_Pad1.20x1.40mm_HandSolder | 0.3 | 0.6 | TE Connectivity | 279-CRG0805F120R | https://www.mouser.es/ProductDetail/TE-Connectivity-Holswort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
R10, R12, R15, R17, R23, R25 | 6 | 2K2 | Resistor_SMD:R_0805_2012Metric_Pad1.20x1.40mm_HandSolder | 0.2 | 1.2000000000000002 | TE Connectivity | 279-CRG0805F2K2 | https://www.mouser.es/ProductDetail/TE-Connectivity-Holswort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
SW1 | 1 | SW_Push | Pulsador:1301931424 | 0.36 | 0.36 | Schurter | 693-1301.9314.24 | https://www.mouser.es/ProductDetail/Schurter/1301931424?qs=G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
U1 | 1 | ATmega2560-16AU | Package_QFP:TQFP-100_14x14mm_P0.5mm |  | 0
U2 | 1 | NCP1117-5.0_TO252 | Package_TO_SOT_SMD:TO-252-2 | 0.76 | 0.76 | Onsemi | 863-NCP1117DT50G | https://www.mouser.es/ProductDetail/onsemi/NCP1117DT50G?qs=G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
U3, U4 | 2 | MCP2515-I/SO | MCP2515-I_SO:SOIC127P1030X265-18N | 2.4500000000000002 | 4.9000000000000004 | Microchip | 579-MCP2515-I/SO | https://www.mouser.es/ProductDetail/Microchip-Technology-Atm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
U5, U6 | 2 | ISO1050DUB | Package_SO:SOP-8_6.62x9.15mm_P2.54mm | 6.86 | 13.72 | Texas Instruments | 595-ISO1050DUB | https://www.mouser.es/ProductDetail/Texas-Instruments/ISO105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
Y1 | 1 | 16 MHz | Crystal 8MHz:ECS-80-32-1X | 0.48 | 0.48 | IQD | 449-LFXTAL027945BULK | https://www.mouser.es/ProductDetail/IQD/LFXTAL027945Bulk?qs=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
Y2, Y3 | 2 | 8 MHz | Crystal 8MHz:ECS-80-32-1X | 0.69 | 1.38 | ECS | 520-HCU800-20X | https://www.mouser.es/ProductDetail/520-HCU800-20X

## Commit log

2022-12-11 Añadido diseño PCB master AMS
2022-12-11 Añadido diseño PCB BMS zeva
2023-01-24 Generated gerber files for BMS Zeva
